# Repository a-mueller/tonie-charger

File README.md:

# Tonie Box charger and station

The main goal was to mount our toniebox onto the bed-frame so we can use it for bedtime. Later I wanted to see how hard it was to create a 9V USB-C charger
instead of the included factory charger. I haven't received the board yet, so can't confirm if it works but will update the repo once I have a working version.

The 3D model consists of 2 parts and can be found in the `/3dPrinting` folder. You will have to get some m2 insets if you want to screw them together and most
likely adjust the spacing for the `bed-attachemnt` part so it fits your bed.

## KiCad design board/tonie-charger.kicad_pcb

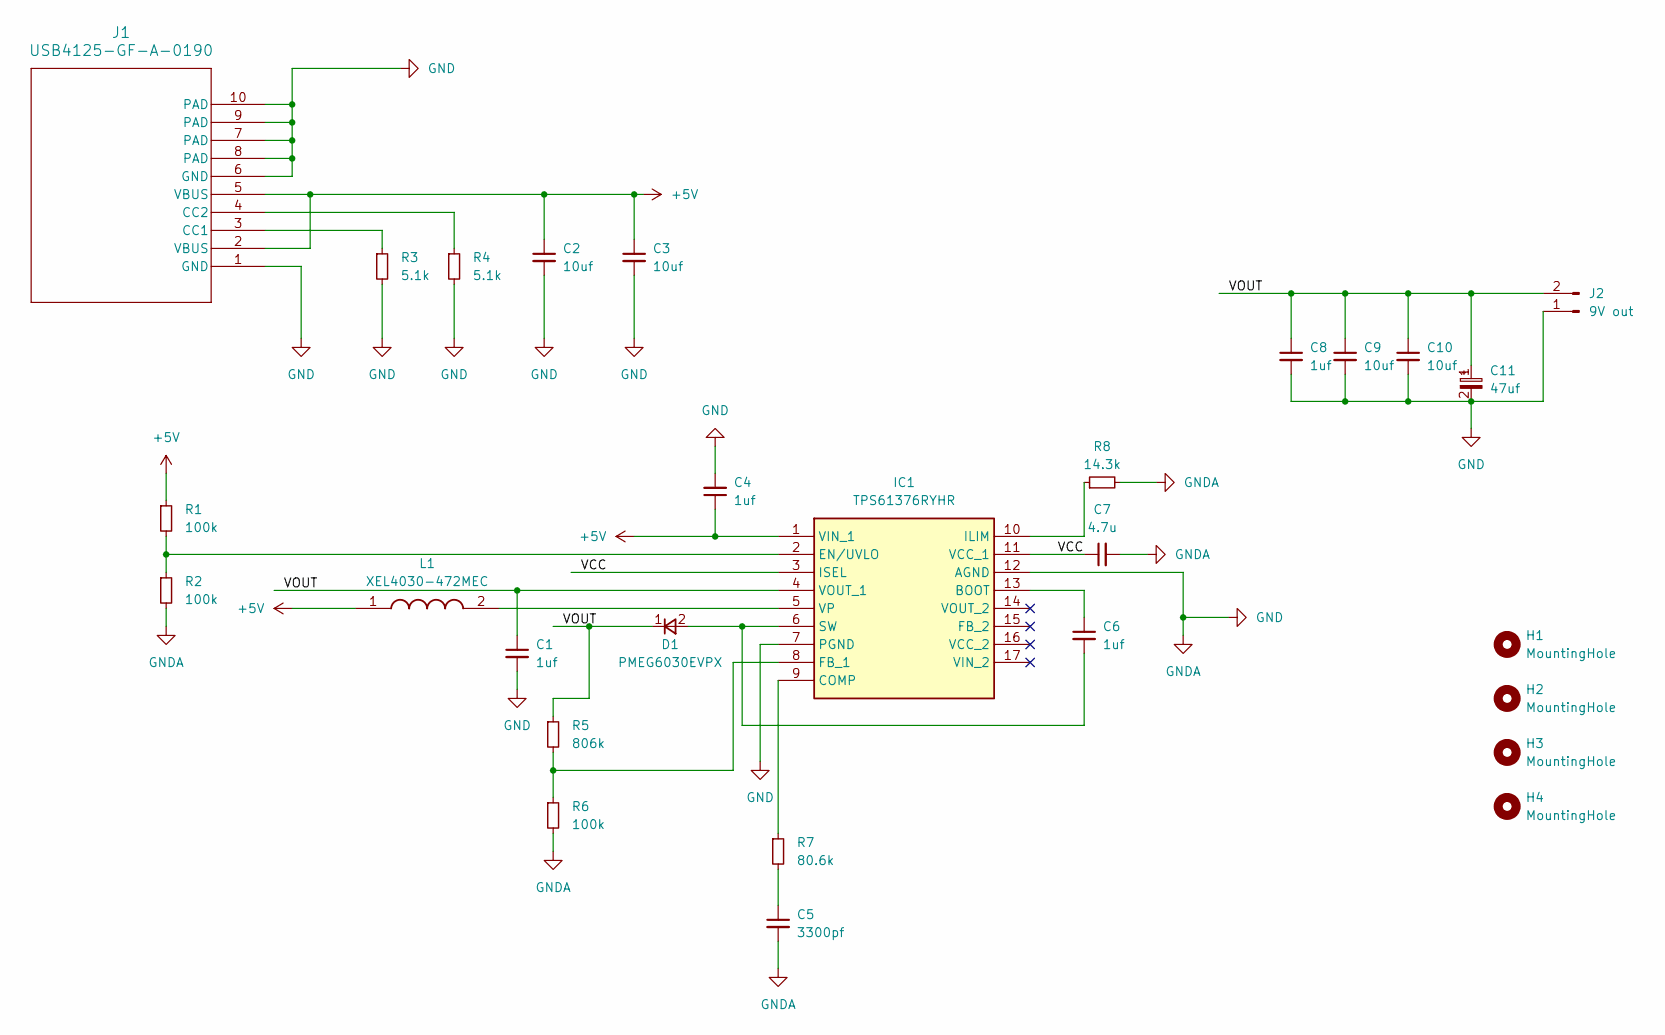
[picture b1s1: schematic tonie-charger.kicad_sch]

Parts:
C1, C4, C6, C8: 1uf; C_0402_1005Metric
C2, C3, C9, C10: 10uf; C_0805_2012Metric
C5: 3300pf; C_0603_1608Metric
C7: 4.7u; C_0603_1608Metric
C11: 47uf; EEE1AA220WR
D1: PMEG6030EVPX
H1, H2, H3, H4: MountingHole; MountingHole_2.2mm_M2
IC1: TPS61376RYHR; Mouser Part Number 595-TPS61376RYHR
J1: USB4125-GF-A-0190; CONN6_125-GF-A-0190_GCT
J2: 9V out; JST_XH_B2B-XH-AM_1x02_P2.50mm_Vertical
L1: XEL4030-472MEC; XEL4030472MEC; Mouser Part Number 994-XEL4030-472MEC
R1, R2, R6: 100k; R_0603_1608Metric
R3, R4: 5.1k; R_0603_1608Metric
R5: 806k; R_0603_1608Metric
R7: 80.6k; R_0603_1608Metric
R8: 14.3k; R_0603_1608Metric

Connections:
+5V: C2.1, C3.1, C4.1, IC1.1 (VIN_1), J1.2 (VBUS), J1.5 (VBUS), L1.1, R1.1
/VCC: C7.1, IC1.3 (ISEL), IC1.11 (VCC_1)
/VOUT: C1.1, C8.1, C9.1, C10.1, C11.1, D1.1 (K), IC1.4 (VOUT_1), J2.2, R5.1
GND: C1.2, C2.2, C3.2, C4.2, C5.2, C7.2, C8.2, C9.2, C10.2, C11.2, IC1.7 (PGND), IC1.12 (AGND), J1.1 (GND), J1.6 (GND), J1.7 (PAD), J1.8 (PAD), J1.9 (PAD), J1.10 (PAD), J2.1, R2.2, R3.2, R4.2, R6.2, R8.2
unnamed: C5.1, R7.2
unnamed: C6.2, D1.2 (A), IC1.6 (SW)
unnamed: C6.1, IC1.13 (BOOT)
unnamed: IC1.9 (COMP), R7.1
unnamed: IC1.2 (EN/UVLO), R1.2, R2.1
unnamed: IC1.8 (FB_1), R5.2, R6.1
unnamed: IC1.10 (ILIM), R8.1
unnamed: IC1.5 (VP), L1.2
unnamed: J1.3 (CC1), R3.1
unnamed: J1.4 (CC2), R4.1

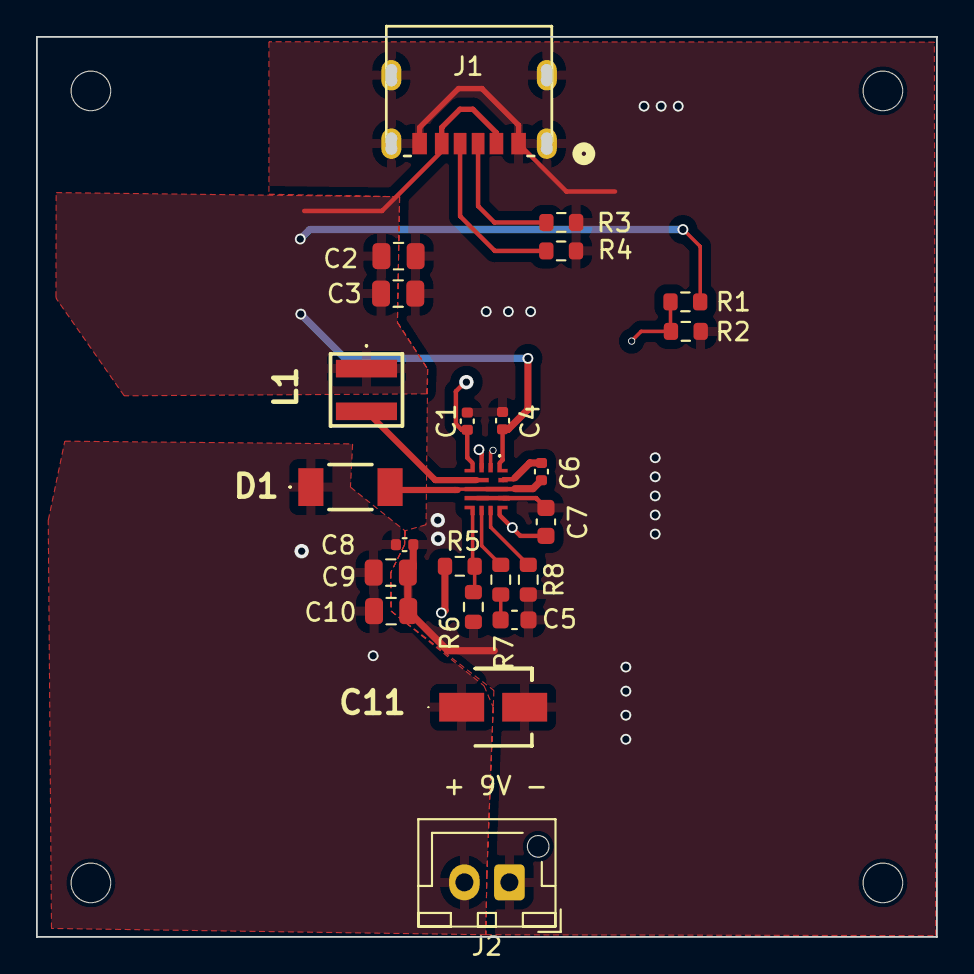
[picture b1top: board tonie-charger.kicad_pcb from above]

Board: 4 copper layers, 49.5 x 49.5 mm, 28 parts (0 on the bottom side), 14 nets.

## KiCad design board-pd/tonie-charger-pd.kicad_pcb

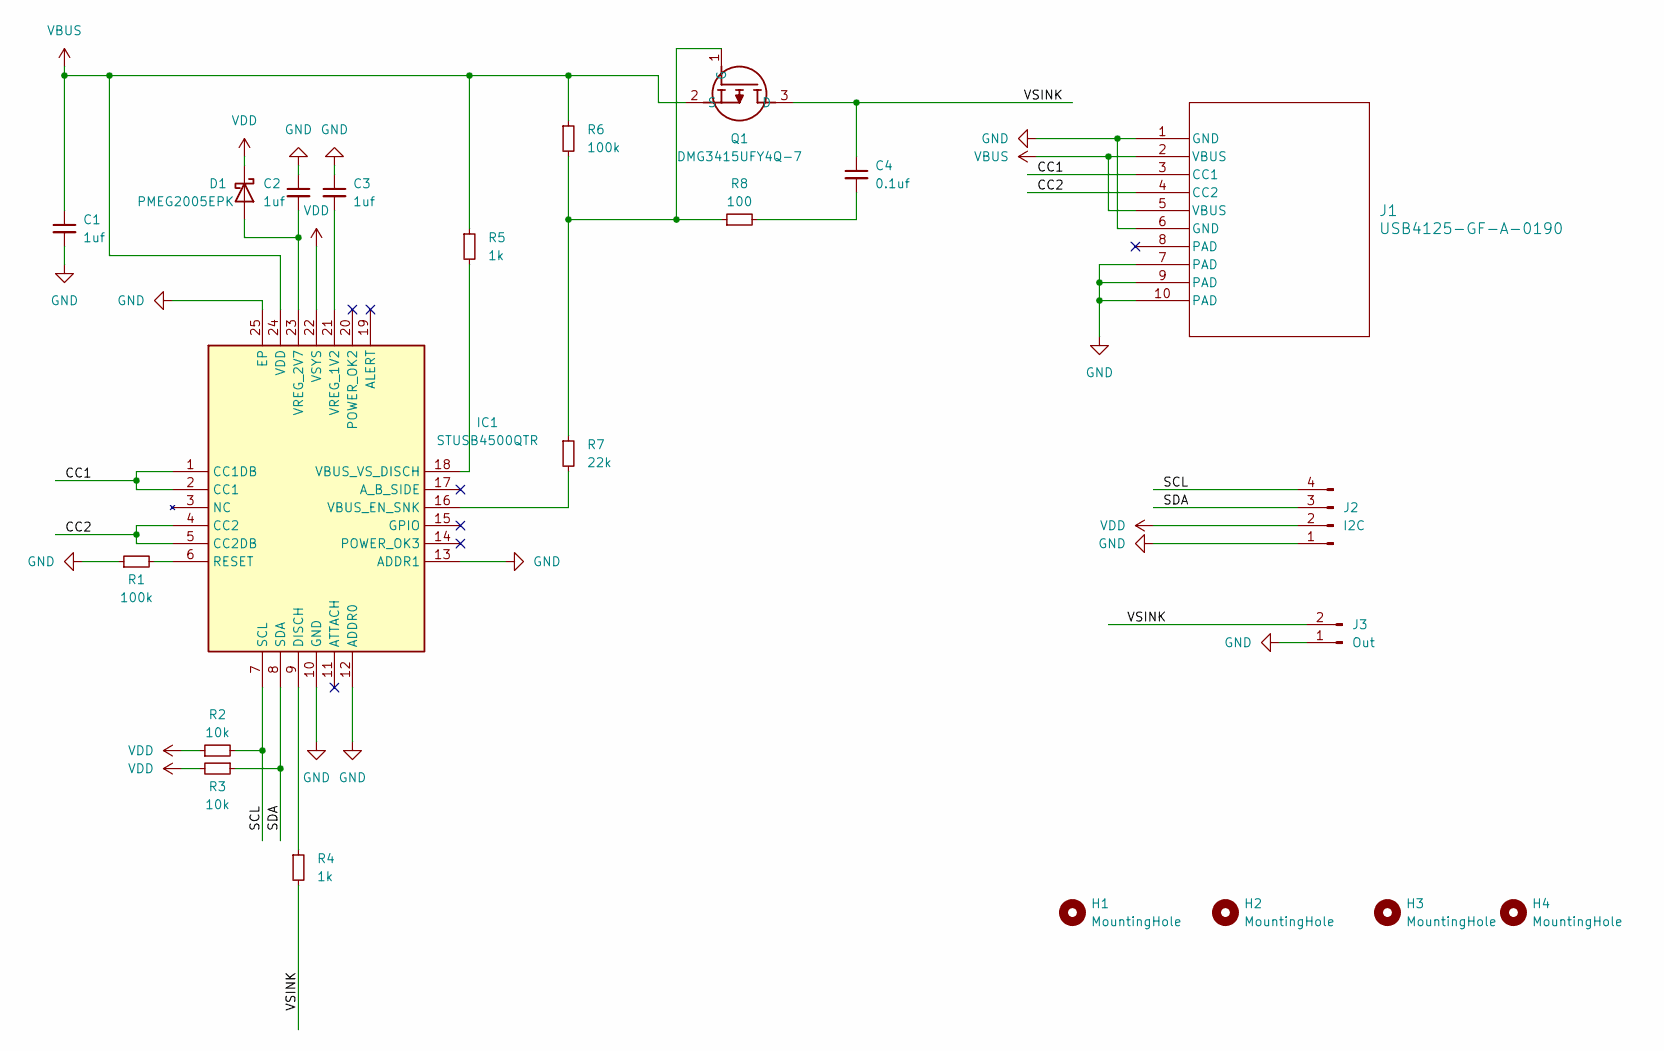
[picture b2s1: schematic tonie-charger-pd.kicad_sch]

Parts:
C1, C2, C3: 1uf; C_0603_1608Metric
C4: 0.1uf; C_0603_1608Metric
D1: PMEG2005EPK; PMEG2005EPKQYL
H1, H2, H3, H4: MountingHole; MountingHole_2.2mm_M2
IC1: STUSB4500QTR; QFN50P400X400X100-25N-D; Manufacturer_Part_Number STUSB4500QTR
J1: USB4125-GF-A-0190; CONN6_125-GF-A-0190_GCT
J2: I2C; JST_PH_B4B-PH-K_1x04_P2.00mm_Vertical
J3: Out; JST_XA_B02B-XASK-1_1x02_P2.50mm_Vertical
Q1: DMG3415UFY4Q-7; DMG3415UFY47; Manufacturer_Part_Number DMG3415UFY4Q-7
R1, R6: 100k; R_0603_1608Metric
R2, R3: 10k; R_0603_1608Metric
R4, R5: 1k; R_0603_1608Metric
R7: 22k; R_0603_1608Metric
R8: 100; R_0603_1608Metric

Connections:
/CC1: IC1.1 (CC1DB), IC1.2 (CC1), J1.3 (CC1)
/CC2: IC1.4 (CC2), IC1.5 (CC2DB), J1.4 (CC2)
/SCL: IC1.7 (SCL), J2.4, R2.2
/SDA: IC1.8 (SDA), J2.3, R3.1
/VSINK: C4.1, J3.2, Q1.3 (D), R4.2
GND: C1.2, C2.1, C3.1, IC1.10 (GND), IC1.12 (ADDR0), IC1.13 (ADDR1), IC1.25 (EP), J1.1 (GND), J1.6 (GND), J1.7 (PAD), J1.9 (PAD), J1.10 (PAD), J2.1, J3.1, R1.1
unnamed: C4.2, R8.2
unnamed: C2.2, D1.2 (A), IC1.23 (VREG_2V7)
unnamed: IC1.9 (DISCH), R4.1
unnamed: IC1.6 (RESET), R1.2
unnamed: IC1.16 (VBUS_EN_SNK), R7.2
unnamed: IC1.18 (VBUS_VS_DISCH), R5.2
unnamed: C3.2, IC1.21 (VREG_1V2)
unnamed: Q1.1 (G), R6.2, R7.1, R8.1
VBUS: C1.1, IC1.24 (VDD), J1.2 (VBUS), J1.5 (VBUS), Q1.2 (S), R5.1, R6.1
VDD: D1.1 (K), IC1.22 (VSYS), J2.2, R2.1, R3.2

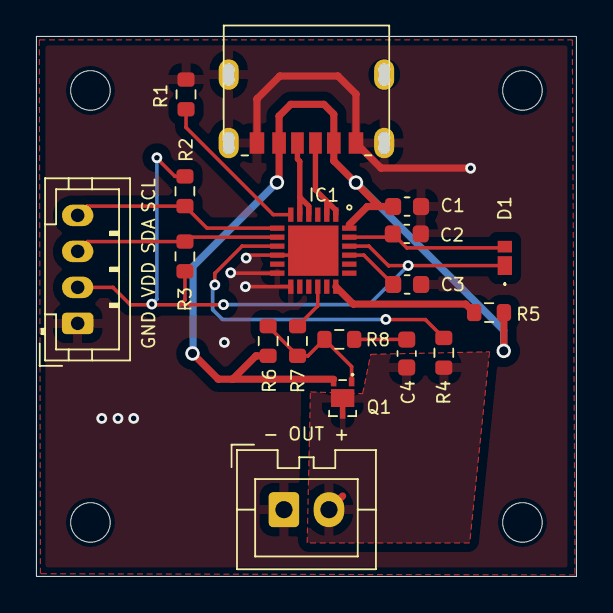
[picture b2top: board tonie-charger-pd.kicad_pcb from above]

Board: 2 copper layers, 29.4 x 29.4 mm, 22 parts (0 on the bottom side), 16 nets.

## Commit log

2024-04-02 creates repo
2024-04-02 adds board & 3d models
2024-04-02 adds some documentation
2024-04-02 add license
2024-04-19 adds flash code
